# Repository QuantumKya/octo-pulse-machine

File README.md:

# octo-pulse-machine
A handheld minigame device parodying Squid Beatz from Splatoon

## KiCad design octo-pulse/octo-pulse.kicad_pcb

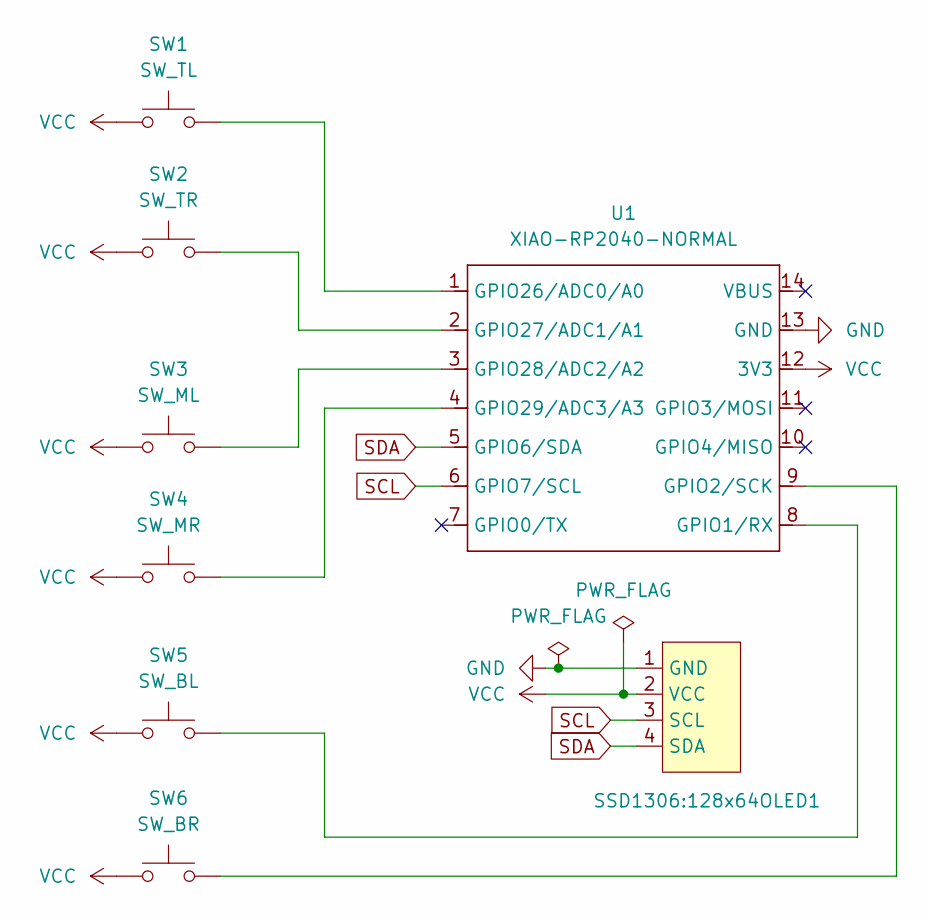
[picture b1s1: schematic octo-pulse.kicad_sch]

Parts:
SSD1306:128x64OLED1: Adafruit_SSD1306_1.3''
SW1: SW_TL; SW_B3U-3000P-B_OMR
SW2: SW_TR; SW_B3U-3000P-B_OMR
SW3: SW_ML; B3U-1000P
SW4: SW_MR; B3U-1000P
SW5: SW_BL; B3U-1000P
SW6: SW_BR; B3U-1000P
U1: XIAO-RP2040-NORMAL; XIAO-RP2040-DIP

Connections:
GND: SSD1306:128x64OLED1.1 (GND), U1.13 (GND)
unnamed: SW5.2, U1.8 (GPIO1/RX)
unnamed: SW6.2, U1.9 (GPIO2/SCK)
unnamed: SW1.2, U1.1 (GPIO26/ADC0/A0)
unnamed: SW2.2, U1.2 (GPIO27/ADC1/A1)
unnamed: SW3.2, U1.3 (GPIO28/ADC2/A2)
unnamed: SW4.2, U1.4 (GPIO29/ADC3/A3)
SCL: SSD1306:128x64OLED1.3 (SCL), U1.6 (GPIO7/SCL)
SDA: SSD1306:128x64OLED1.4 (SDA), U1.5 (GPIO6/SDA)
VCC: SSD1306:128x64OLED1.2 (VCC), SW1.1, SW2.1, SW3.1, SW4.1, SW5.1, SW6.1, U1.12 (3V3)

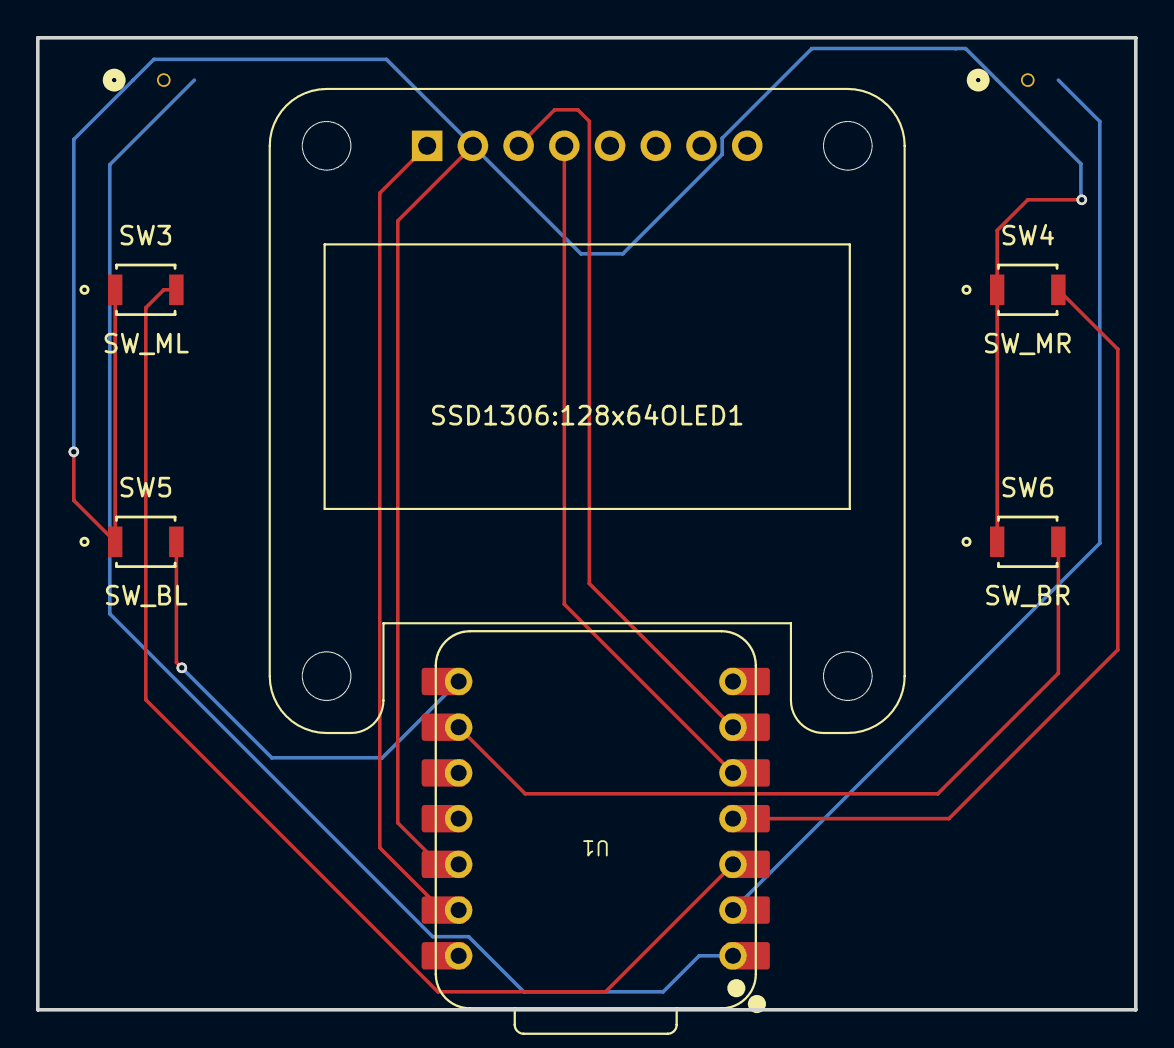
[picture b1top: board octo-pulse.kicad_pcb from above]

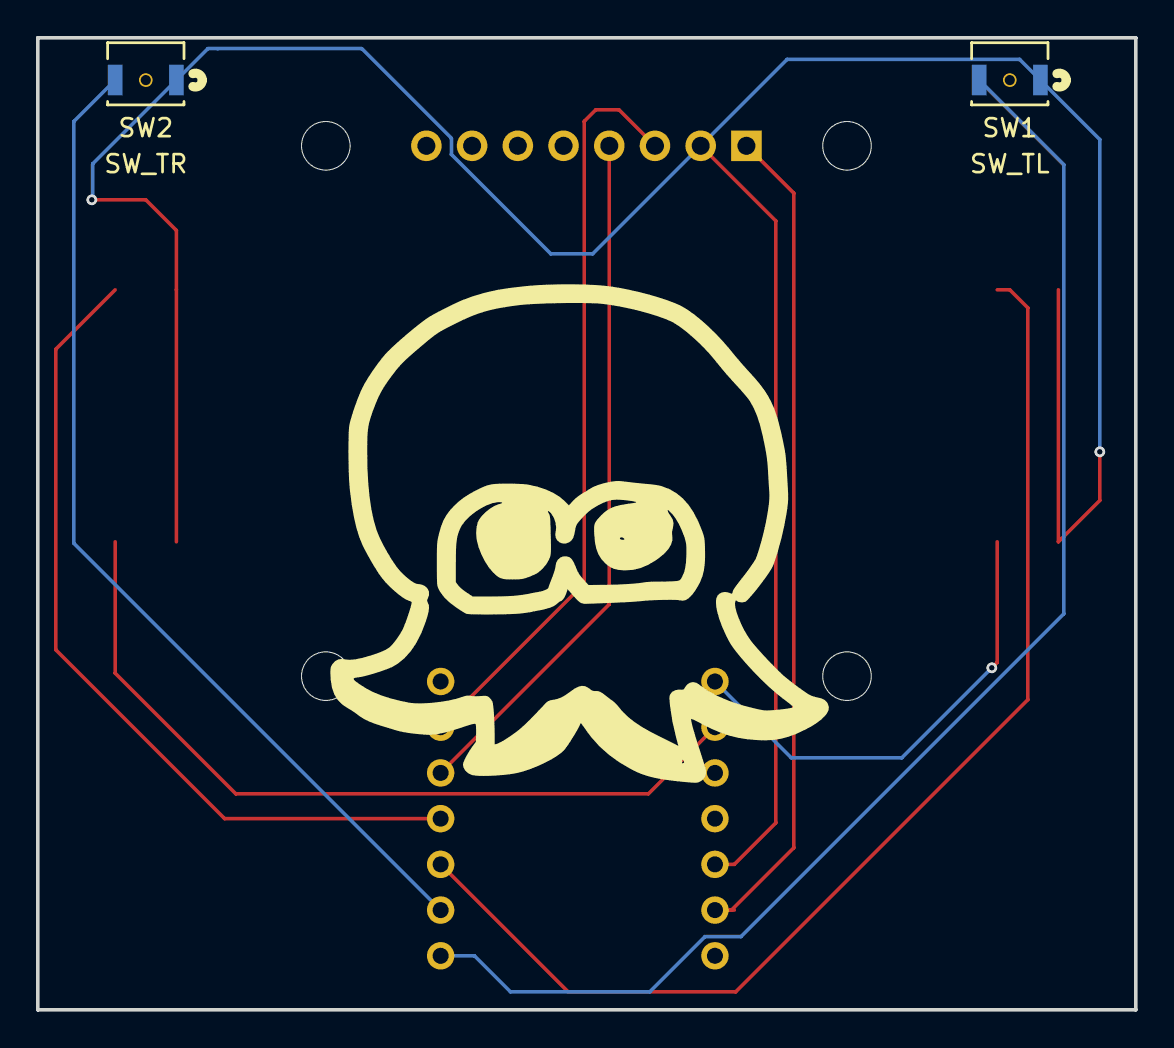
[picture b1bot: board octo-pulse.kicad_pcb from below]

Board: 2 copper layers, 61.0 x 54.0 mm, 8 parts (2 on the bottom side), 10 nets.

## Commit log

2026-05-24 added kicad project folder
2026-06-02 Fully wired PCB in KiCad
2026-06-02 Finished & decorated PCB, onto programming!
2026-06-03 replaced switches on PCB with new ones: B3U-1000P & B3U-3000P-B
